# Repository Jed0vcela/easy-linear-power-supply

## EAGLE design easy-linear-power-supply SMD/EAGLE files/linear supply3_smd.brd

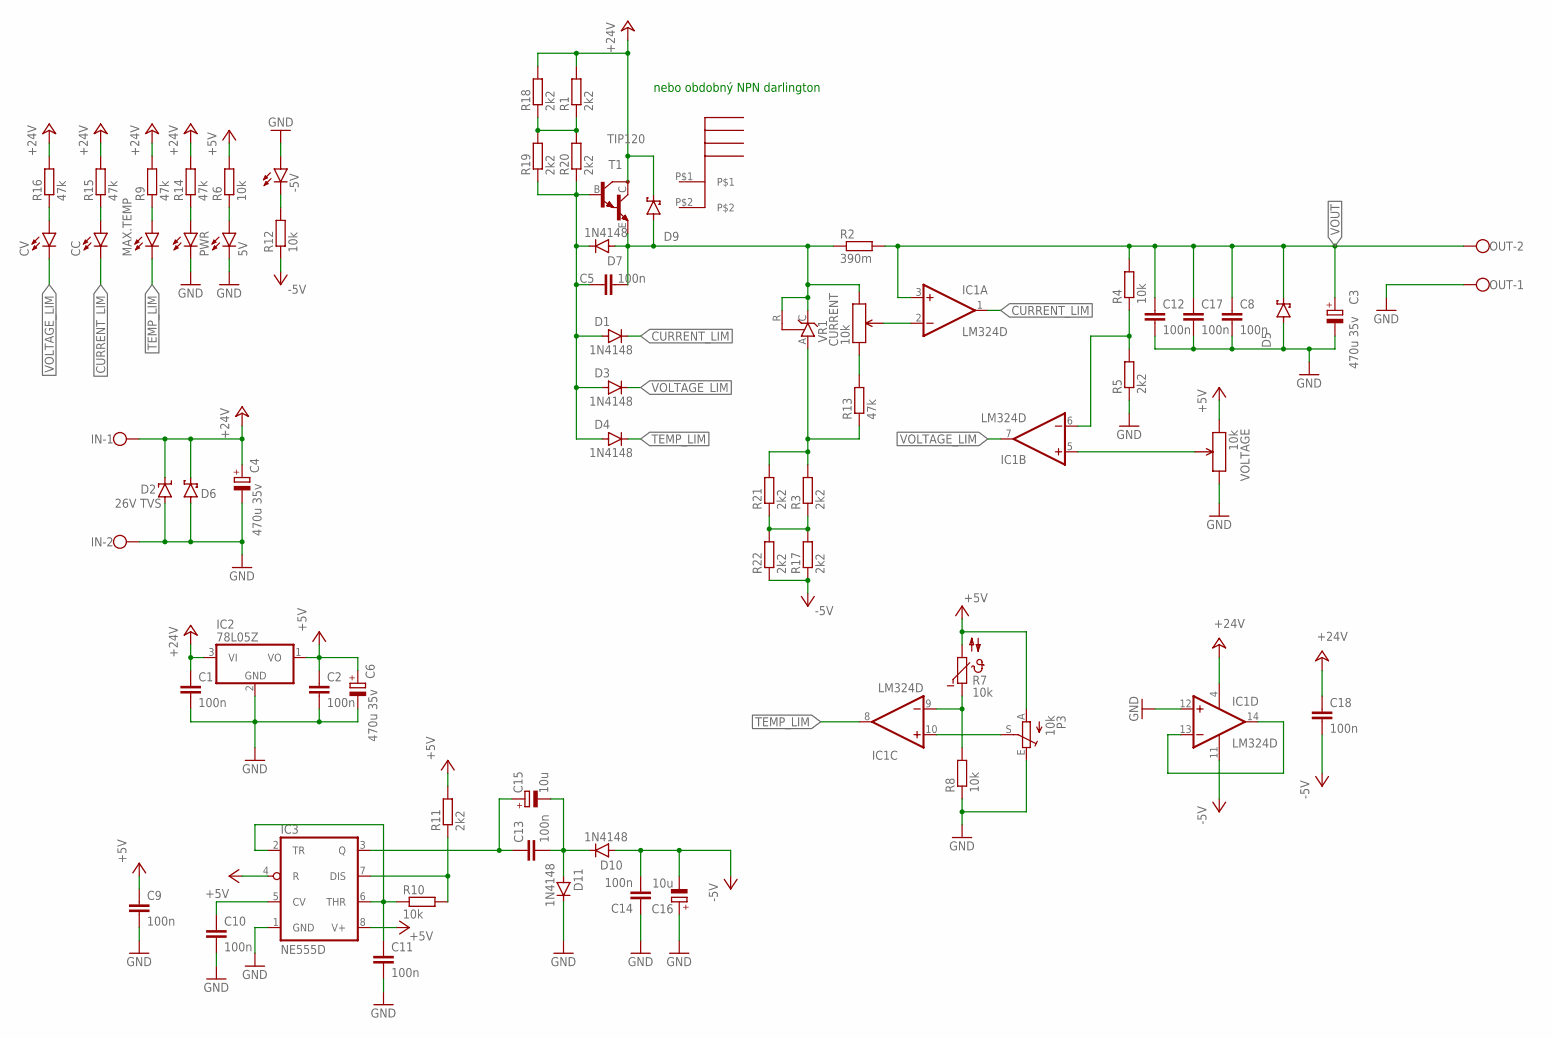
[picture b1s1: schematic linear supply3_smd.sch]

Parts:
5V: LEDCHIP-LED0805; CHIP-LED0805
-5V: LEDCHIP-LED0805; CHIP-LED0805
C1, C2, C5, C9, C10, C11, C13, C14, C18: 100n; C0805
C3, C4, C6: 470u 35v; E5-10,5
C8: 100n; C050-050X075
C12, C17: 100n; C1206
C15, C16: 10u; E2,5-6
CC: LEDCHIP-LED0805; CHIP-LED0805
CURRENT: 10k; THRU_PCW_POT
CV: LEDCHIP-LED0805; CHIP-LED0805
D1, D3, D4, D7, D10, D11: 1N4148; SOD80C
D2: 26V TVS; SMBJ
D5, D6, D9: SCHOTTKY-DIODESMC; SMC
IC1: LM324D; SO14
IC2: 78L05Z; TO92
IC3: NE555D; SO08
IN: W237-102
MAX.TEMP: LEDCHIP-LED0805; CHIP-LED0805
OUT: W237-102
P3: 10k; CA6V
PWR: LEDCHIP-LED0805; CHIP-LED0805
R1, R3, R5, R11, R17, R18, R19, R20, R21, R22: 2k2; R0805
R2: 390m; 0411/12
R4, R6, R8, R10, R12: 10k; R0805
R7: 10k; P642
R9, R13, R14, R15, R16: 47k; R0805
T1: TIP120; SOT93
U$1: RAD-DY-KY/3; RAD-DY-KY/3HEATSINK
VOLTAGE: 10k; THRU_PCW_POT
VR1: TL431CLP; TO92-CLP

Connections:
+5V: C2.1, C6.+, C9.1, IC2.1 (VO), IC3.4 (R), IC3.8 (V+), P3.A, R6.2, R7.2, R11.2, VOLTAGE.P$1 (1)
+24V: C1.1, C4.+, C18.1, D2.C, D6.C, D9.C, IC1.4 (V+), IC2.3 (VI), IN.1, R1.2, R9.2, R14.2, R15.2, R16.2, R18.2, T1.C
-5V: C14.2, C16.-, C18.2, D10.A, IC1.11 (V-), R12.1, R17.1, R22.1
CURRENT_LIM: CC.C, D1.C, IC1.1 (OUT)
GND: 5V.C, -5V.A, C1.2, C2.2, C3.-, C4.-, C6.-, C8.2, C9.2, C10.2, C11.2, C12.2, C14.1, C16.+, C17.2, D2.A, D5.A, D6.A, D11.C, IC1.12 (+IN), IC2.2 (GND), IC3.1 (GND), IN.2, OUT.1, P3.E, PWR.C, R5.1, R8.1, VOLTAGE.P$3 (3)
MAX: R3.2, R13.1, R21.2, VR1.A
MIN: C5.2, CURRENT.P$3 (3), D7.A, D9.A, R2.1, T1.E, VR1.C, VR1.R
unnamed: C5.1, D1.A, D3.A, D4.A, D7.C, R19.1, R20.1, T1.B
unnamed: PWR.A, R14.1
unnamed: C11.1, IC3.2 (TR), IC3.6 (THR), R10.1
unnamed: IC1.9 (-IN), R7.1, R8.2
unnamed: IC1.6 (-IN), R4.1, R5.2
unnamed: 5V.A, R6.1
unnamed: IC1.5 (+IN), VOLTAGE.P$2 (2)
unnamed: IC1.10 (+IN), P3.S
unnamed: CURRENT.P$2 (2), IC1.2 (-IN)
unnamed: MAX.TEMP.A, R9.1
unnamed: IC1.13 (-IN), IC1.14 (OUT)
unnamed: IC3.7 (DIS), R10.2, R11.1
unnamed: C13.1, C15.+, IC3.3 (Q)
unnamed: C10.1, IC3.5 (CV)
unnamed: C13.2, C15.-, D10.C, D11.A
unnamed: -5V.C, R12.2
unnamed: CURRENT.P$1 (1), R13.2
unnamed: CC.A, R15.1
unnamed: CV.A, R16.1
unnamed: R1.1, R18.1, R19.2, R20.2
unnamed: R3.1, R17.2, R21.1, R22.2
TEMP_LIM: D4.C, IC1.8 (OUT), MAX.TEMP.C
VOLTAGE_LIM: CV.C, D3.C, IC1.7 (OUT)
VOUT: C3.+, C8.1, C12.1, C17.1, D5.C, IC1.3 (+IN), OUT.2, R2.2, R4.2

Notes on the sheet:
nebo obdobný NPN darlington

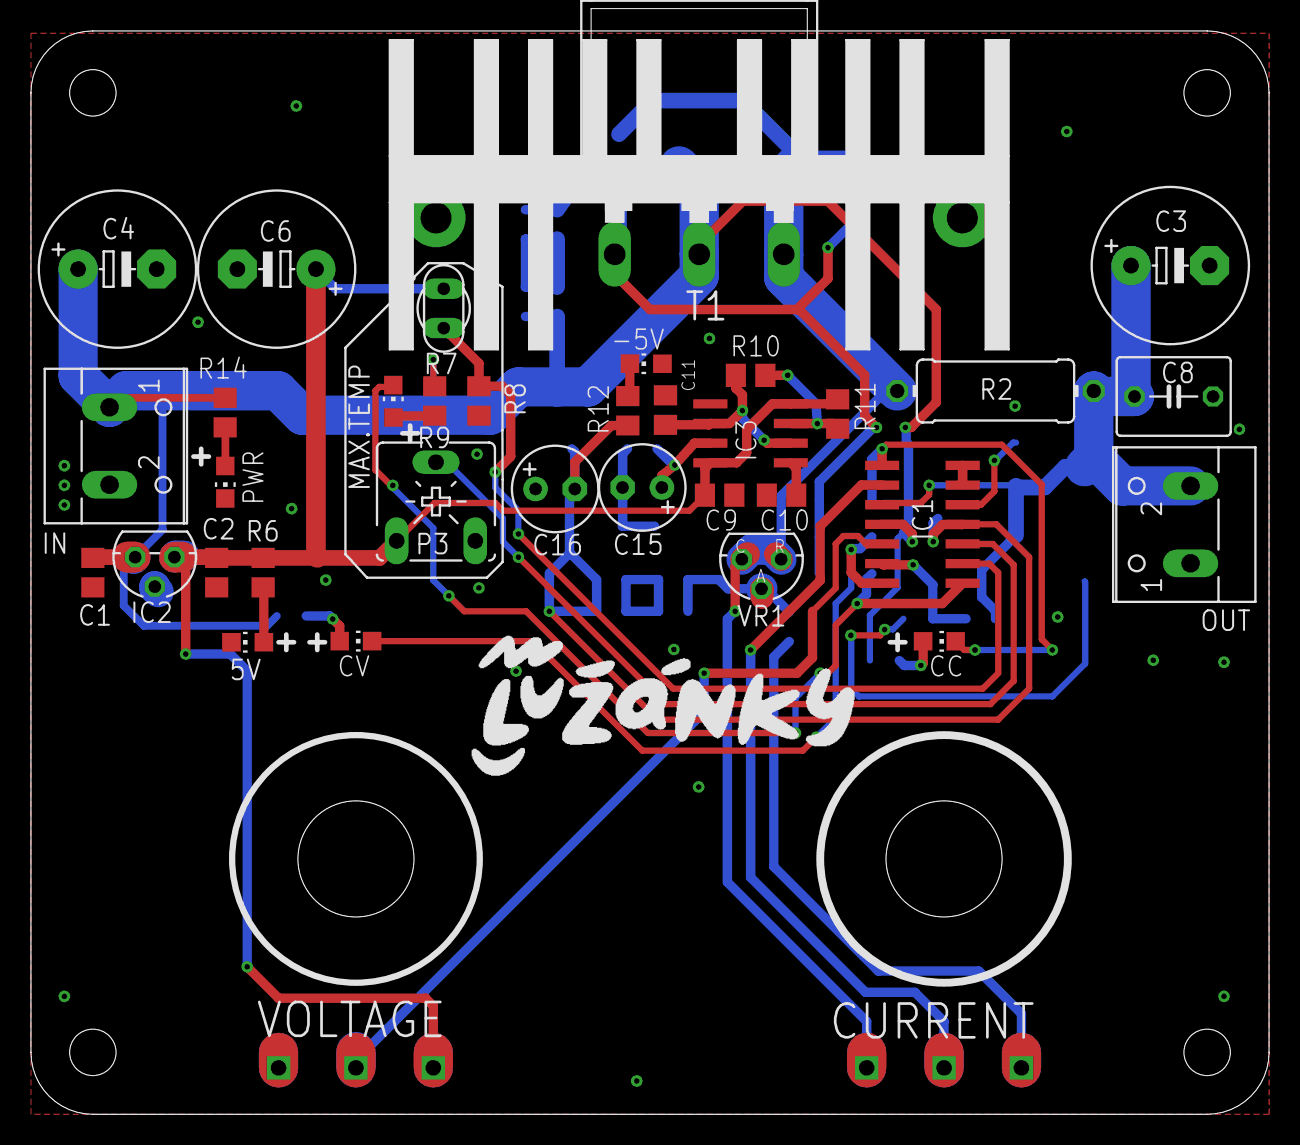
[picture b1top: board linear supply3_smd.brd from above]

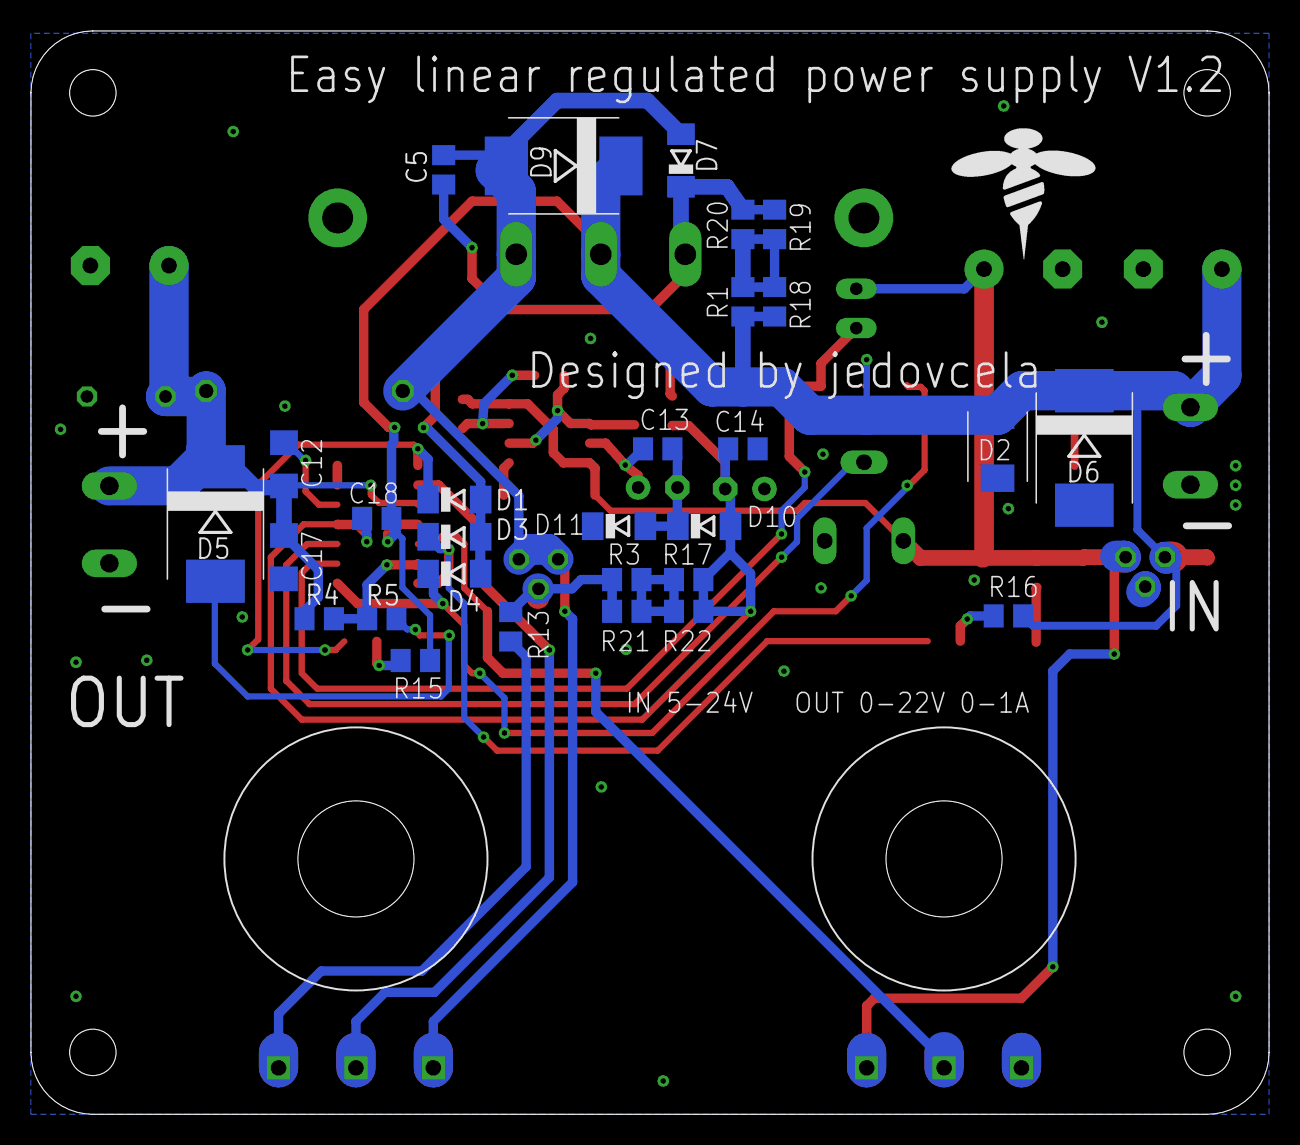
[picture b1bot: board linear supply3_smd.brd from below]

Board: 2 copper layers, 80.0 x 70.0 mm, 66 parts (31 on the bottom side), 31 nets.

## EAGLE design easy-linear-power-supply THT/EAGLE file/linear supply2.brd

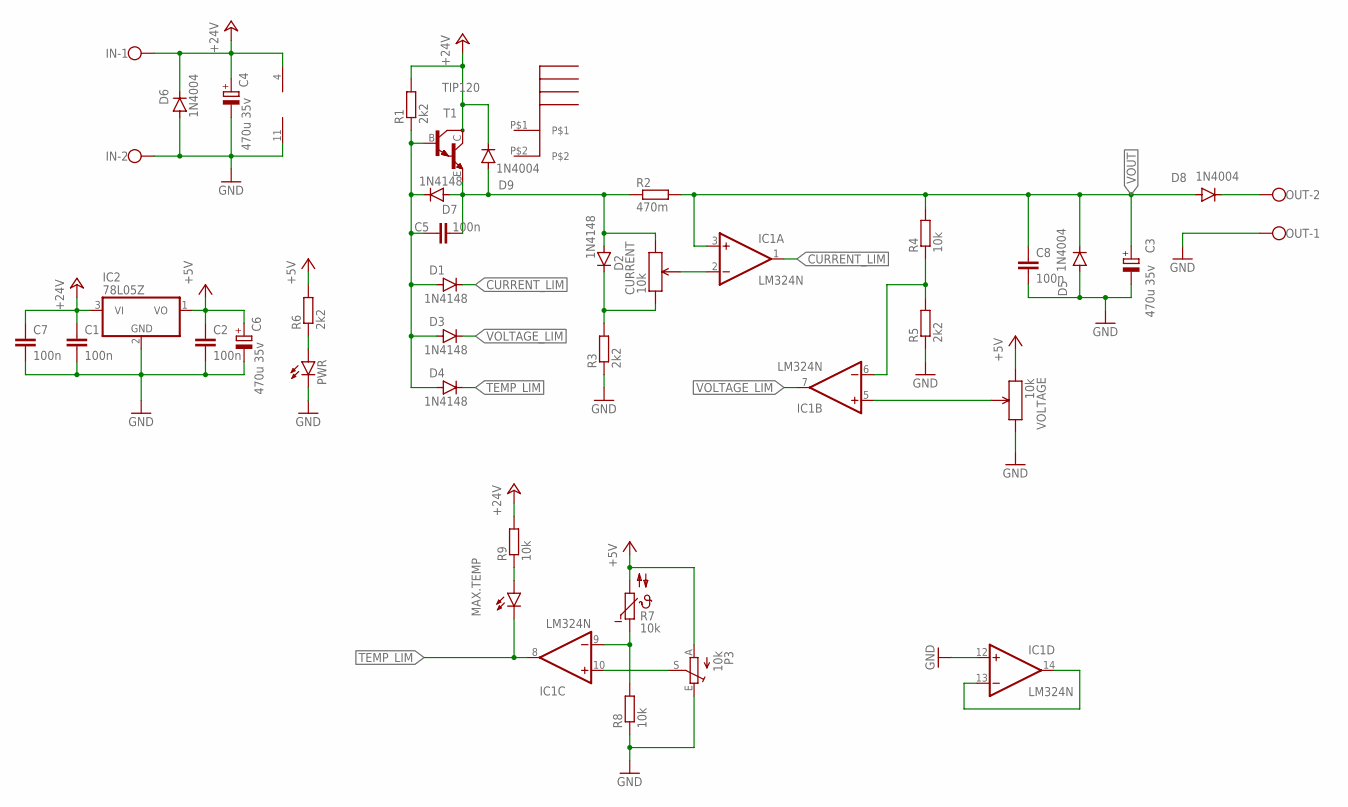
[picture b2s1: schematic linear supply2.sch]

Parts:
C1, C2, C5: 100n; C050-024X044
C3, C4, C6: 470u 35v; E5-10,5
C7: 100n; C1206K
C8: 100n; C050-050X075
CURRENT: 10k; THRU_PCW_POT
D1, D2, D3, D4, D7: 1N4148; DO35-7
D5, D6, D8, D9: 1N4004; DO41-10
IC1: LM324N; DIL14
IC2: 78L05Z; TO92
IN: W237-102
MAX.TEMP: LED3MM
OUT: W237-102
P3: 10k; CA6V
PWR: LED3MM
R1, R3, R5, R6: 2k2; 0207/10
R2: 470m; 0411/12
R4, R8, R9: 10k; 0207/10
R7: 10k; P642
T1: TIP120; SOT93
U$1: RAD-DY-KY/3; RAD-DY-KY/3HEATSINK
VOLTAGE: 10k; THRU_PCW_POT

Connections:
+5V: C2.1, C6.+, IC2.1 (VO), P3.A, R6.2, R7.2, VOLTAGE.P$1 (1)
+24V: C1.1, C4.+, C7.1, D6.C, D9.C, IC1.4 (V+), IC2.3 (VI), IN.1, R1.2, R9.2, T1.C
CURRENT_LIM: D1.C, IC1.1 (OUT)
GND: C1.2, C2.2, C3.-, C4.-, C6.-, C7.2, C8.2, D5.A, D6.A, IC1.11 (V-), IC1.12 (+IN), IC2.2 (GND), IN.2, OUT.1, P3.E, PWR.K (C), R3.1, R5.1, R8.1, VOLTAGE.P$3 (3)
MAX: CURRENT.P$1 (1), D2.C, R3.2
MIN: C5.2, CURRENT.P$3 (3), D2.A, D7.A, D9.A, R2.1, T1.E
unnamed: C5.1, D1.A, D3.A, D4.A, D7.C, R1.1, T1.B
unnamed: D8.C, OUT.2
unnamed: IC1.9 (-IN), R7.1, R8.2
unnamed: IC1.6 (-IN), R4.1, R5.2
unnamed: PWR.A, R6.1
unnamed: IC1.5 (+IN), VOLTAGE.P$2 (2)
unnamed: IC1.10 (+IN), P3.S
unnamed: CURRENT.P$2 (2), IC1.2 (-IN)
unnamed: MAX.TEMP.A, R9.1
unnamed: IC1.13 (-IN), IC1.14 (OUT)
TEMP_LIM: D4.C, IC1.8 (OUT), MAX.TEMP.K (C)
VOLTAGE_LIM: D3.C, IC1.7 (OUT)
VOUT: C3.+, C8.1, D5.C, D8.A, IC1.3 (+IN), R2.2, R4.2

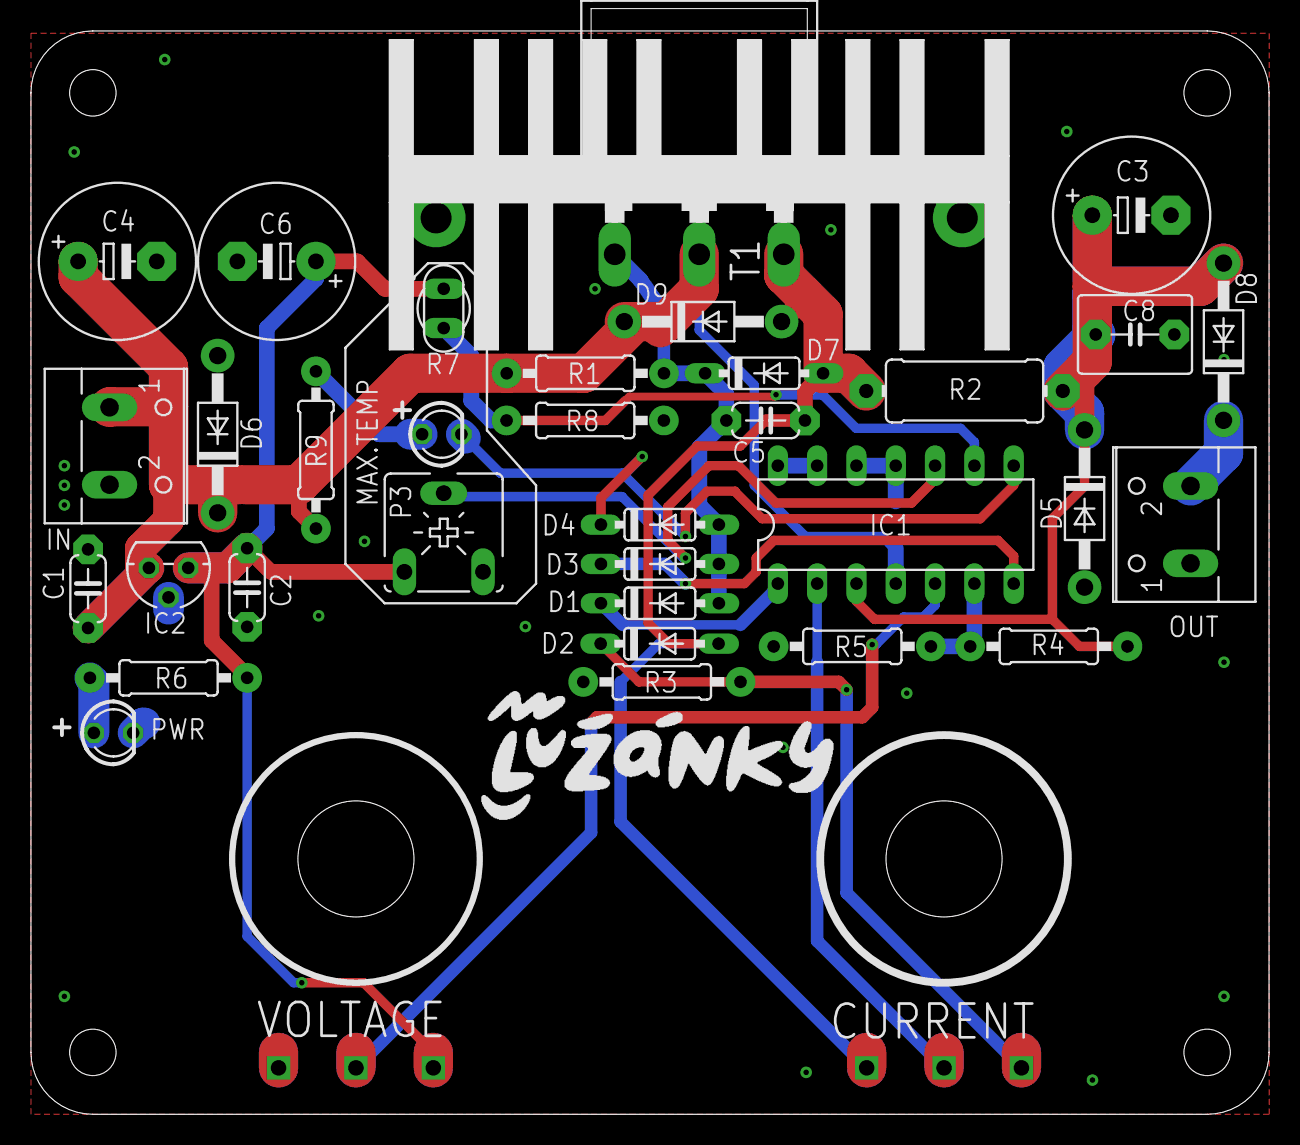
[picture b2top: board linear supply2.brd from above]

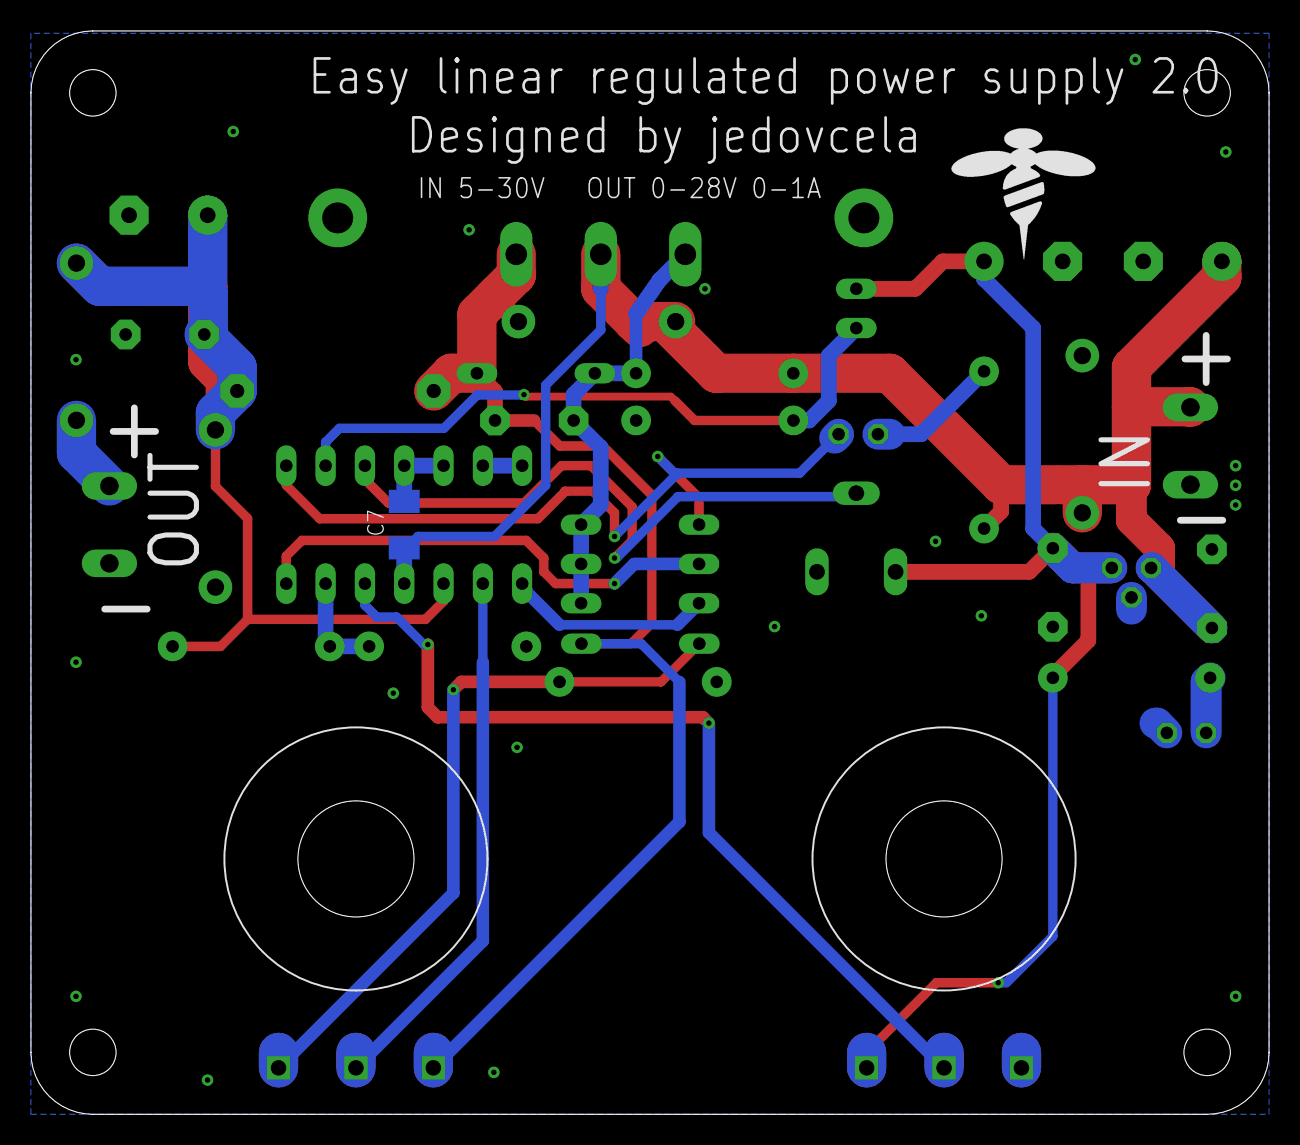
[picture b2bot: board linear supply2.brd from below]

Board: 2 copper layers, 80.0 x 70.0 mm, 37 parts (3 on the bottom side), 19 nets.

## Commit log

2024-04-13 Create EAGLE files
